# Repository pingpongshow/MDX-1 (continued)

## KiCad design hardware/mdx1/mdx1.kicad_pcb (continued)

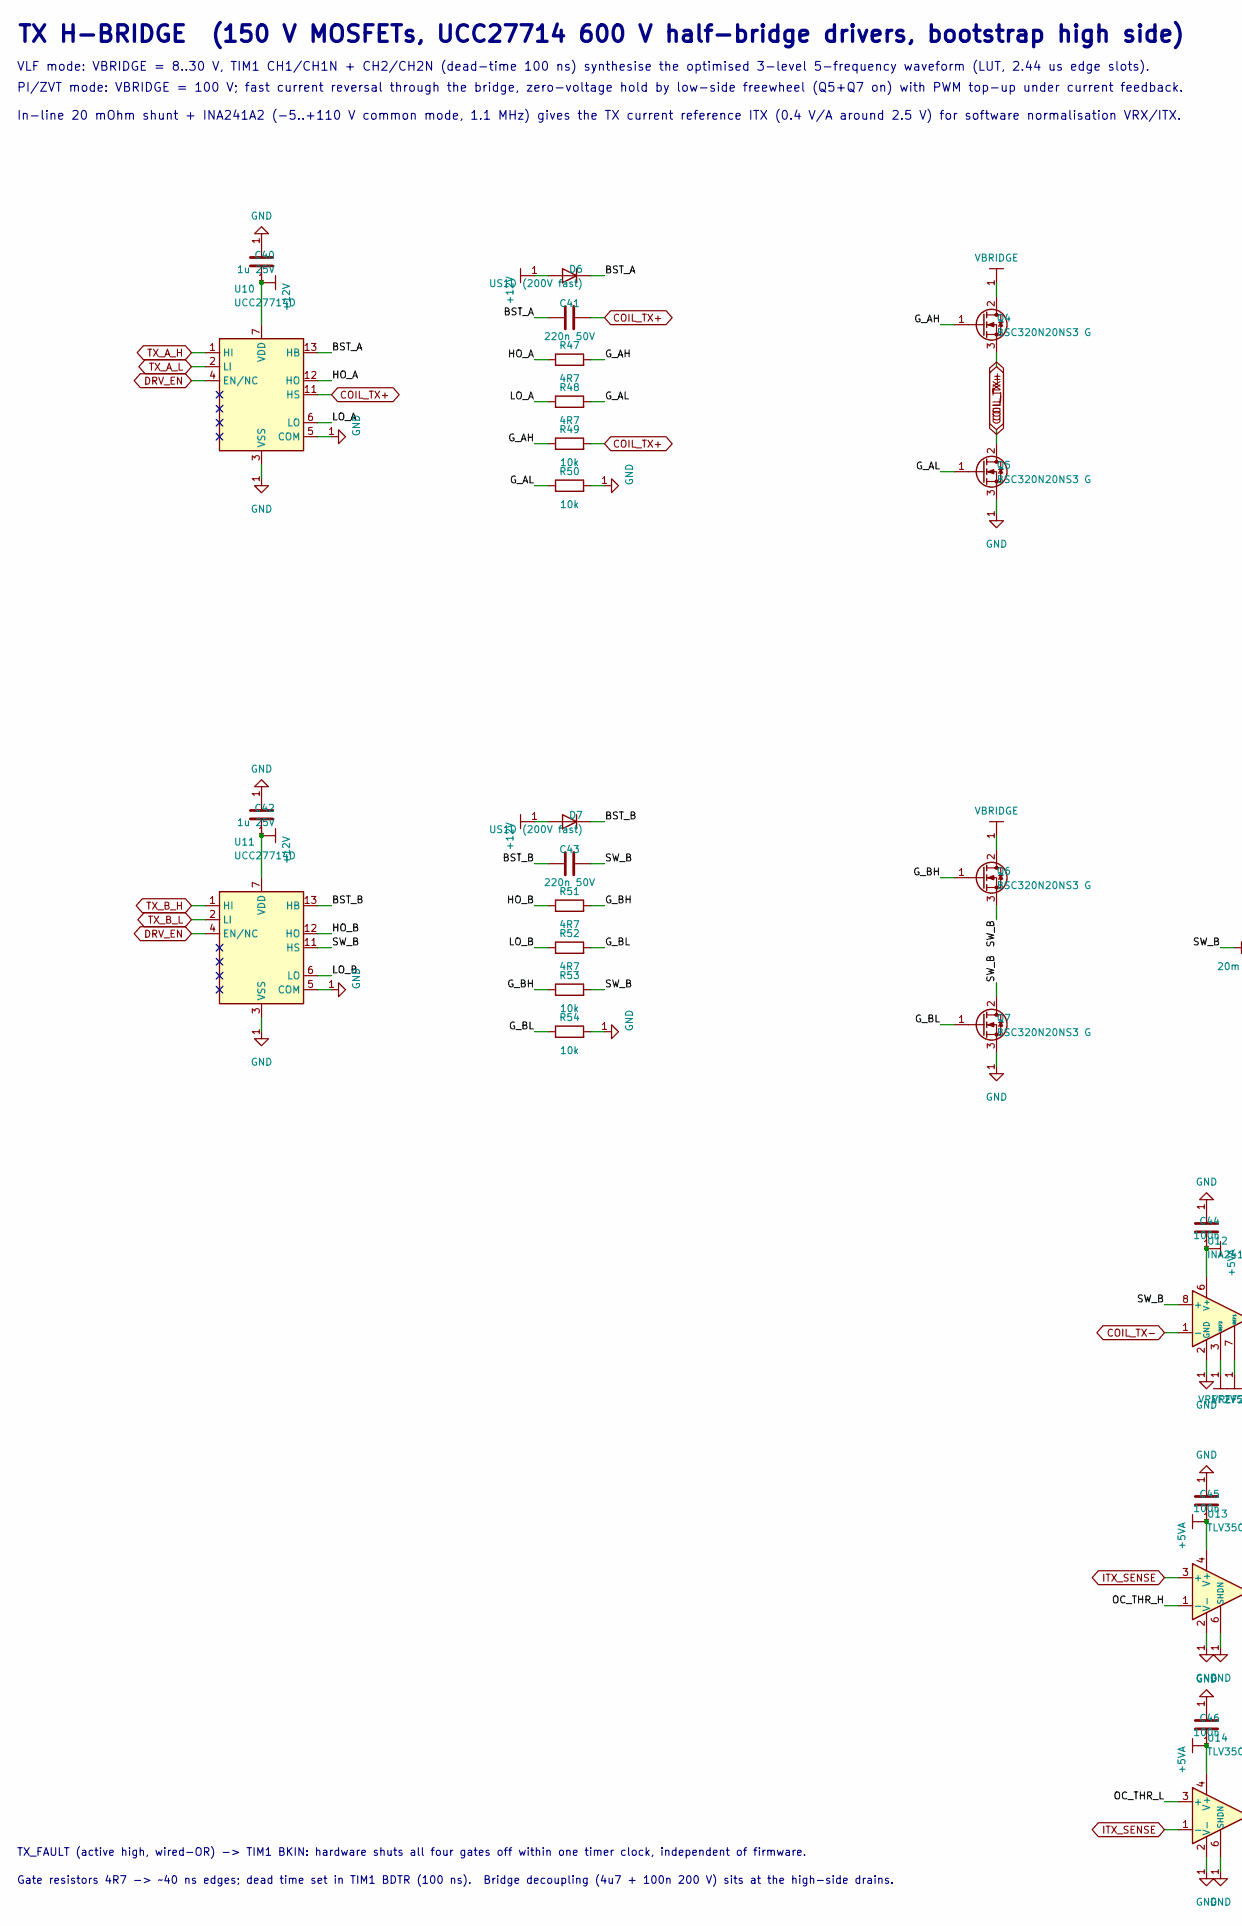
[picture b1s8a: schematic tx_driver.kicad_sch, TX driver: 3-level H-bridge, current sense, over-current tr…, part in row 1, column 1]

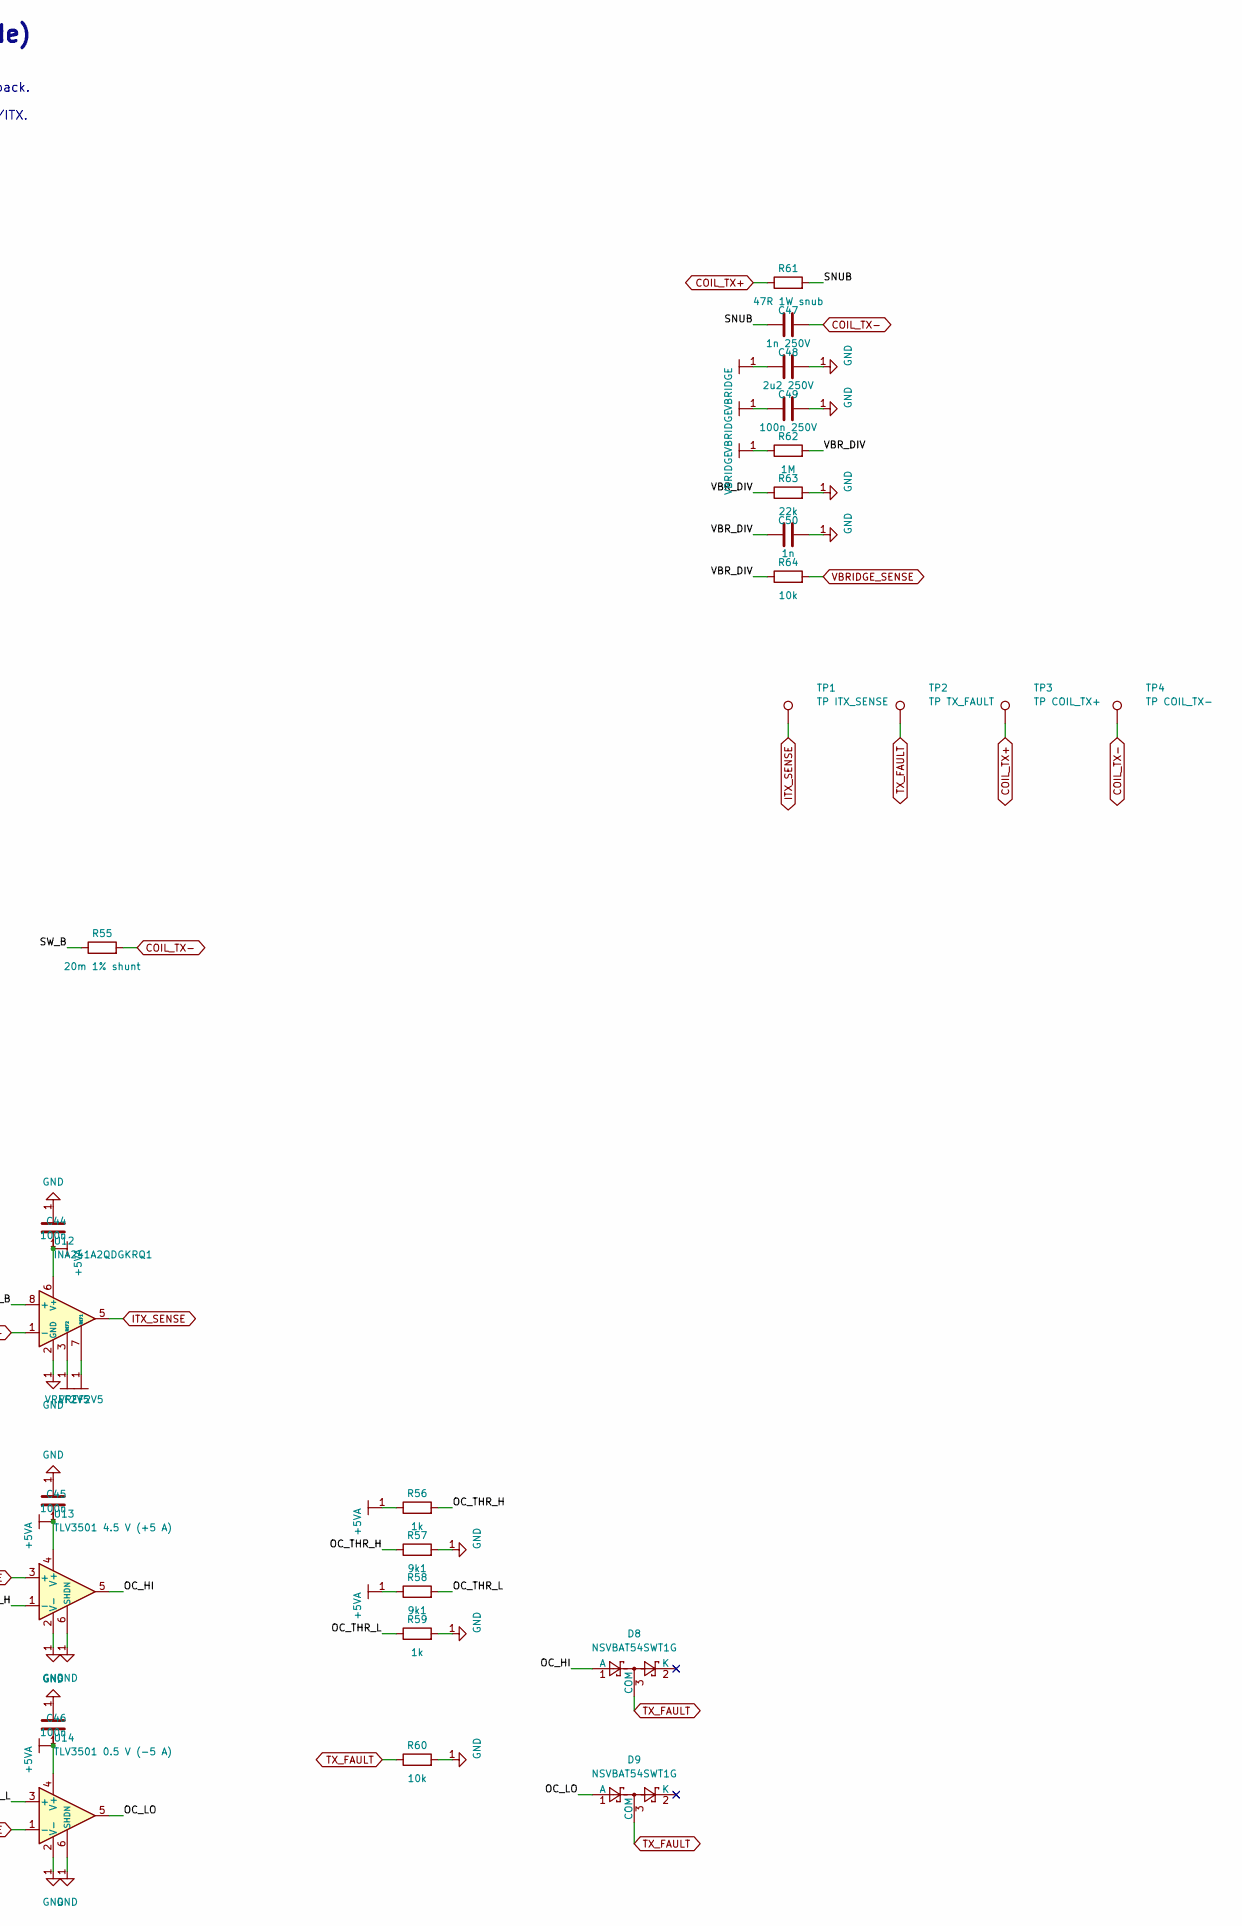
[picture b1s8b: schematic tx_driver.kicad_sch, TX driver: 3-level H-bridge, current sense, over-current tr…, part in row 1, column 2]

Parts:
C40, C42: 1u 25V; C_0603_1608Metric
C41, C43: 220n 50V; C_0603_1608Metric
C44, C45, C46: 100n; C_0402_1005Metric
C47: 1n 250V; C_1206_3216Metric
C48: 2u2 250V; C_2220_5750Metric
C49: 100n 250V; C_1206_3216Metric
C50: 1n; C_0402_1005Metric
D6, D7: US1D (200V fast); D_SMA
D8, D9: NSVBAT54SWT1G; SOT-323_SC-70
Q4, Q5, Q6, Q7: BSC320N20NS3 G; Infineon_PG-TDSON-8_6.15x5.15mm
R47, R48, R51, R52: 4R7; R_0402_1005Metric
R49, R50, R53, R54, R60, R64: 10k; R_0402_1005Metric
R55: 20m 1% shunt; R_2512_6332Metric
R56, R59: 1k; R_0402_1005Metric
R57, R58: 9k1; R_0402_1005Metric
R61: 47R 1W snub; R_2512_6332Metric
R62: 1M; R_0402_1005Metric
R63: 22k; R_0402_1005Metric
TP1: TP ITX_SENSE; TestPoint_Pad_D1.5mm
TP2: TP TX_FAULT; TestPoint_Pad_D1.5mm
TP3: TP COIL_TX+; TestPoint_Pad_D1.5mm
TP4: TP COIL_TX-; TestPoint_Pad_D1.5mm
U10, U11: UCC27714D; SOIC-14_3.9x8.7mm_P1.27mm
U12: INA241A2QDGKRQ1; VSSOP-8_3x3mm_P0.65mm
U13: TLV3501 4.5 V (+5 A); SOT-23-6
U14: TLV3501 0.5 V (-5 A); SOT-23-6

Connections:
+5VA: C44.1, C45.1, C46.1, R56.1, R58.1, U12.6 (V+), U13.4 (V+), U14.4 (V+); also elsewhere on the board
+12V: C40.1, C42.1, D6.2 (A), D7.2 (A), U10.7 (VDD), U11.7 (VDD); also elsewhere on the board
/TX driver: 3-level H-bridge, current sense, over-current trip/BST_A: C41.1, D6.1 (K), U10.13 (HB)
/TX driver: 3-level H-bridge, current sense, over-current trip/BST_B: C43.1, D7.1 (K), U11.13 (HB)
/TX driver: 3-level H-bridge, current sense, over-current trip/G_AH: Q4.1 (G), R47.2, R49.1
/TX driver: 3-level H-bridge, current sense, over-current trip/G_AL: Q5.1 (G), R48.2, R50.1
/TX driver: 3-level H-bridge, current sense, over-current trip/G_BH: Q6.1 (G), R51.2, R53.1
/TX driver: 3-level H-bridge, current sense, over-current trip/G_BL: Q7.1 (G), R52.2, R54.1
/TX driver: 3-level H-bridge, current sense, over-current trip/HO_A: R47.1, U10.12 (HO)
/TX driver: 3-level H-bridge, current sense, over-current trip/HO_B: R51.1, U11.12 (HO)
/TX driver: 3-level H-bridge, current sense, over-current trip/LO_A: R48.1, U10.6 (LO)
/TX driver: 3-level H-bridge, current sense, over-current trip/LO_B: R52.1, U11.6 (LO)
/TX driver: 3-level H-bridge, current sense, over-current trip/OC_HI: D8.1 (A), U13.5
/TX driver: 3-level H-bridge, current sense, over-current trip/OC_LO: D9.1 (A), U14.5
/TX driver: 3-level H-bridge, current sense, over-current trip/OC_THR_H: R56.2, R57.1, U13.1 (-)
/TX driver: 3-level H-bridge, current sense, over-current trip/OC_THR_L: R58.2, R59.1, U14.3 (+)
/TX driver: 3-level H-bridge, current sense, over-current trip/SNUB: C47.1, R61.2
/TX driver: 3-level H-bridge, current sense, over-current trip/SW_B: C43.2, Q6.3 (S), Q7.2 (D), R53.2, R55.1, U11.11 (HS), U12.8 (+)
/TX driver: 3-level H-bridge, current sense, over-current trip/VBR_DIV: C50.1, R62.2, R63.1, R64.1
COIL_TX+: C41.2, Q4.3 (S), Q5.2 (D), R49.2, R61.1, TP3.1 (1_1), U10.11 (HS); also elsewhere on the board
COIL_TX-: C47.2, R55.2, TP4.1 (1_1), U12.1 (-); also elsewhere on the board
DRV_EN: U10.4 (EN/NC), U11.4 (EN/NC); also elsewhere on the board
ITX_SENSE: TP1.1 (1_1), U12.5, U13.3 (+), U14.1 (-); also elsewhere on the board
TX_A_H: U10.1 (HI); also elsewhere on the board
TX_A_L: U10.2 (LI); also elsewhere on the board
TX_B_H: U11.1 (HI); also elsewhere on the board
TX_B_L: U11.2 (LI); also elsewhere on the board
TX_FAULT: D8.3 (COM), D9.3 (COM), R60.1, TP2.1 (1_1); also elsewhere on the board
VBRIDGE: C48.1, C49.1, Q4.2 (D), Q6.2 (D), R62.1; also elsewhere on the board
VBRIDGE_SENSE: R64.2; also elsewhere on the board
VREF2V5: U12.3 (REF2), U12.7 (REF1); also elsewhere on the board

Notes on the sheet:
TX_FAULT (active high, wired-OR) -> TIM1 BKIN: hardware shuts all four gates off within one timer clock, independent of firmware.
In-line 20 mOhm shunt + INA241A2 (-5..+110 V common mode, 1.1 MHz) gives the TX current reference ITX (0.4 V/A around 2.5 V) for software normalisation VRX/ITX.
Gate resistors 4R7 -> ~40 ns edges; dead time set in TIM1 BDTR (100 ns). Bridge decoupling (4u7 + 100n 200 V) sits at the high-side drains.
VLF mode: VBRIDGE = 8..30 V, TIM1 CH1/CH1N + CH2/CH2N (dead-time 100 ns) synthesise the optimised 3-level 5-frequency waveform (LUT, 2.44 us edge slots).
TX H-BRIDGE (150 V MOSFETs, UCC27714 600 V half-bridge drivers, bootstrap high side)
PI/ZVT mode: VBRIDGE = 100 V; fast current reversal through the bridge, zero-voltage hold by low-side freewheel (Q5+Q7 on) with PWM top-up under current feedback.

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
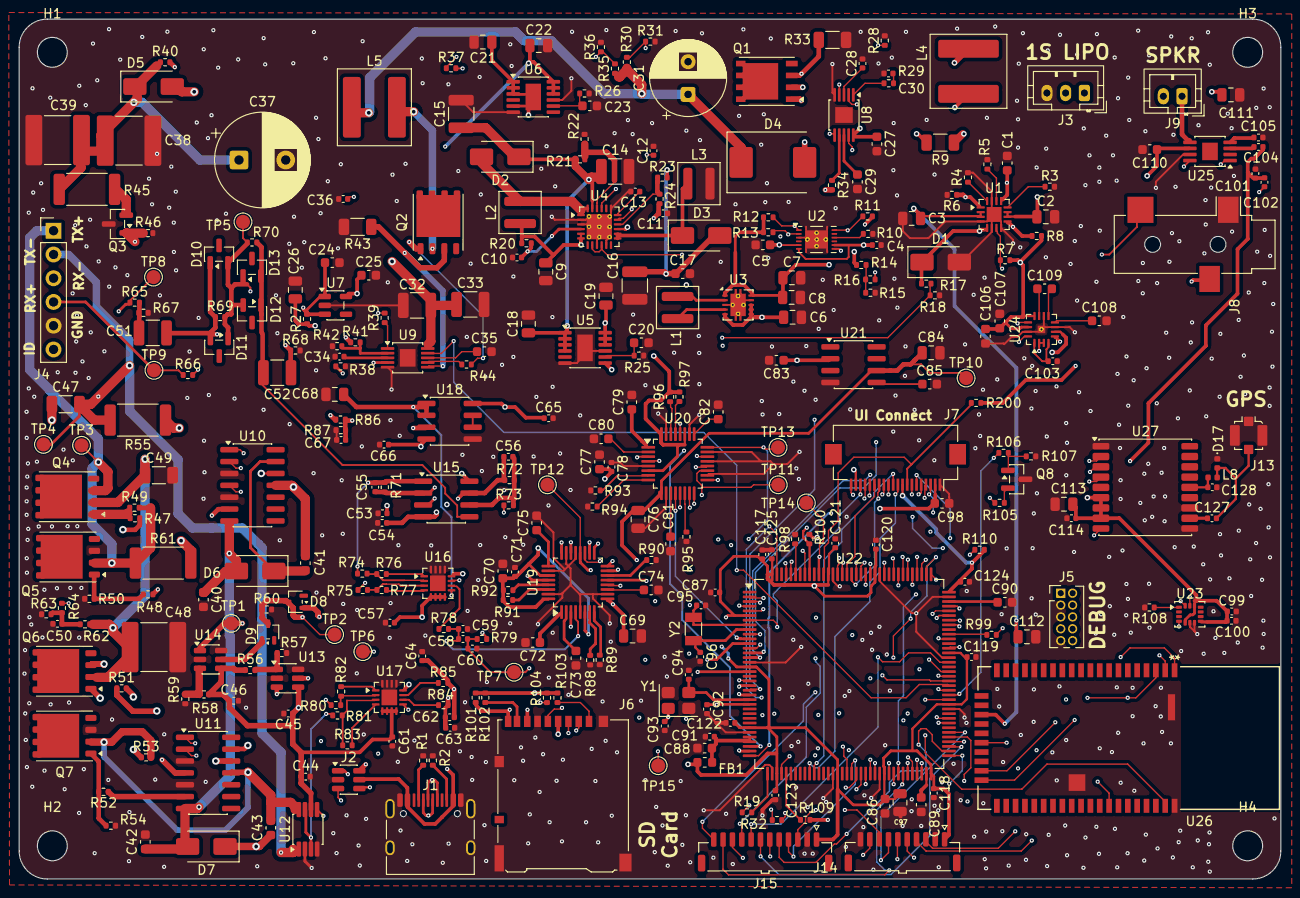
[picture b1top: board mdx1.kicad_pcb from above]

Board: 4 copper layers, 135.0 x 92.0 mm, 325 parts (0 on the bottom side), 250 nets.

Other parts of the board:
H1, H2, H3, H4: MountingHole_3.2mm_M3

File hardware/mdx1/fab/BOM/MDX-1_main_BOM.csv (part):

Comment,Designator,Footprint,Quantity,Manufacturer,MPN,LCSC Part #
"4.7 µF MLCC, 10 V X5R, 10 %","C1,C20,C23,C27,C29,C35,C86",C_0603_1608Metric,7,Taiyo Yuden,LMK107BJ475KA-T,
10 µF 10 V X5R MLCC,"C2,C3,C6,C9,C26,C68,C69,C76,C84,C97,C111,C112,C113",C_0805_2012Metric,13,Samsung Electro-Mechanics,CL21A106KPFNNNG,
100n,"C4,C10,C28,C44,C45,C46,C53,C54,C57,C61,C65,C66,C71,C78,C87,C91,C92,C99,C100,C114,C117,C118,C119,C120,C121,C122,C123,C124,C125",C_0402_1005Metric,29,Murata,GRM155R71H104KE14D,
"1 µF MLCC, 25 V X5R, 10 %","C5,C17,C24,C25,C40,C42,C70,C72,C73,C74,C75,C77,C79,C80,C81,C82,C83,C85,C88,C98,C108,C109,C110",C_0603_1608Metric,23,KYOCERA AVX,06033D105KAT2A,
22u 6.3V,"C7,C8",C_0805_2012Metric,2,TDK,C2012X5R0J226M085AB,
220n,"C11,C34,C104,C105",C_0402_1005Metric,4,Samsung Electro-Mechanics,CL05A224KP5NNNC,
"10 nF MLCC, 50 V X7R, 10 %","C12,C36,C128",C_0402_1005Metric,3,Murata,GRM155R71H103KA88D,
4n7,"C13,C30,C101",C_0402_1005Metric,3,Murata,GRM155R71H472KA01D,
22u 25V,"C14,C15,C16",C_1210_3225Metric,3,Samsung Electro-Mechanics,CL32A226KAJNNWE,
4u7 25V,"C18,C21",C_0805_2012Metric,2,TDK,C2012X5R1E475K125AB,
10u 25V,"C19,C22",C_0805_2012Metric,2,TDK,C2012X5R1V106K085AC,
100u 50V,C31,CP_Radial_D8.0mm_P3.50mm,1,Panasonic,EEU-FC1H101,
10u 50V,C32,C_1210_3225Metric,1,KEMET,C1210C106K5RACTU,
4u7 50V,C33,C_1210_3225Metric,1,Murata,GRM32ER71H475KA88L,
47u 160V,C37,CP_Radial_D10.0mm_P5.00mm,1,Rubycon,160PK47MEFC10X20,
2u2 250V,"C38,C39,C48",C_2220_5750Metric,3,TDK,C5750X7T2E225K250KE,
220n 50V,"C41,C43",C_0603_1608Metric,2,Murata,GRM188R71H224KAC4D,
1n 250V,C47,C_1206_3216Metric,1,Vishay,VPDD202W102K1GV001E,
100n 250V,C49,C_1206_3216Metric,1,Murata,GRM31CR72E104KW03L,
1n,C50,C_0402_1005Metric,1,TDK,C1005C0G1H102J050BA,
1u C0G/film,"C51,C52",C_1210_3225Metric,2,KYOCERA AVX,12103C105KAT2A,
680p C0G,"C55,C56",C_0402_1005Metric,2,Murata,GRM1555C1H681JA01D,
3n3 C0G,"C58,C62",C_0402_1005Metric,2,Murata,GRM1555C1H332JE01D,
330p C0G,"C59,C60,C63,C64",C_0402_1005Metric,4,Murata,GRM1555C1H331JA01D,
1u,"C67,C102,C103",C_0402_1005Metric,3,Samsung Electro-Mechanics,CL05A105KP5NNNC,
2u2,"C89,C90,C106,C107",C_0603_1608Metric,4,Murata,GRM188R61E225KA12D,
10p C0G,"C93,C94",C_0402_1005Metric,2,Murata,GRM1555C1H100JA01D,
6.8p C0G,"C95,C96",C_0402_1005Metric,2,Murata,GRM1555C1H6R8DA01D,
33 pF,C127,C_0402_1005Metric,1,Murata,GRM1555C1H330JA01D,
SMAJ5.0A TVS,D1,D_SMA,1,Littelfuse,SMAJ5.0A-E3/61,
SS34,"D2,D3",D_SMA,2,Vishay,SS34-E3/57T,
B560C 60V 5A,D4,D_SMC,1,Diodes Inc.,B560C-13-F,
STPS2150 150V,D5,D_SMA,1,STMicroelectronics,STPS2150A,
US1D,"D6,D7",D_SMA,2,Vishay,US1D-E3/61T,
NSVBAT54SWT1G,"D8,D9",SOT-323_SC-70,2,onsemi,NSVBAT54SWT1G,
BAS416,"D10,D11,D12,D13",SOT-23,4,Diodes Incorporated,BAS116-7-F,
PESD0402-140,D17,D_0402_1005Metric,1,Nexperia,PESD0402-140,
600R@100MHz,FB1,L_0603_1608Metric,1,Murata,BLM18KG601SN1D,
USB-C 16P,J1,USB_C_Receptacle_HRO_TYPE-C-31-M-12,1,GCT,USB4085-GF-A,
USBLC6-2SC6,J2,SOT-23-6,1,STMicroelectronics,USBLC6-2SC6,
Battery JST-PH 3p,J3,JST_PH_B3B-PH-K_1x03_P2.00mm_Vertical,1,JST,B3B-PH-K-S,
Coil header 1x06 2.54mm,J4,PinHeader_1x06_P2.54mm_Vertical,1,Wurth Elektronik,61300611121,
SWD 10p 1.27mm,J5,PinHeader_2x05_P1.27mm_Vertical,1,Samtec,FTSH-105-01-L-DV-K,
microSD,J6,microSD_HC_Hirose_DM3AT-SF-PEJM5,1,Hirose,DM3AT-SF-PEJM5,
UI link FFC 20p 0.5mm,J7,Hirose_FH12-20S-0.5SH_1x20-1MP_P0.50mm_Horizontal,1,Hirose,FH12-20S-0.5SH(55),
3.5 mm jack,J8,Jack_3.5mm_CUI_SJ-3523-SMT_Horizontal,1,CUI Devices,SJ-3523-SMT-TR,
Speaker 8R,J9,JST_PH_B2B-PH-K_1x02_P2.00mm_Vertical,1,JST,B2B-PH-K-S,
Conn_Coaxial,J13,U.FL_Molex_MCRF_73412-0110_Vertical,1,Molex,73412-0110,
1u5 XAL4020,L1,L_Coilcraft_XAL4020-XXX,1,Coilcraft,XAL4020-152MEC,
4u7 XAL4020,"L2,L3",L_Coilcraft_XAL4020-XXX,2,Coilcraft,XAL4030-472MEC,
22u XAL7050,L4,L_Coilcraft_XAL7050-XXX,1,Coilcraft,XAL7050-223MEC,
47u XAL7050,L5,L_Coilcraft_XAL7050-XXX,1,Coilcraft,XAL7050-473MEC,
27nH,L8,L_0402_1005Metric,1,Murata,LQW15AN27NG00D,
SiR680ADP-T1-UE3,Q1,PowerPAK_SO-8_Single,1,Vishay Siliconix,SIR680ADP-T1-UE3,
BSC190N15NS3,Q2,Infineon_PG-TDSON-8_6.15x5.15mm,1,Infineon,BSC190N15NS3GATMA1,
BSS127S,Q3,SOT-23,1,Diodes Incorporated,BSS127S-7,
BSC320N20NS3 G,"Q4,Q5,Q6,Q7",Infineon_PG-TDSON-8_6.15x5.15mm,4,Infineon,BSC320N20NS3GATMA1,
2N7002,Q8,SOT-23,1,onsemi,2N7002ET1G,
5k1,"R1,R2",R_0402_1005Metric,2,Yageo,RC0402FR-075K1L,
1k1,R3,R_0402_1005Metric,1,Yageo,RC0402FR-071K1L,
887R,R4,R_0402_1005Metric,1,Yageo,RC0402FR-07887RL,
47k,"R5,R17,R36,R101,R102,R103,R104",R_0402_1005Metric,7,Yageo,RC0402FR-0747KL,
10k,"R6,R10,R11,R16,R19,R37,R49,R50,R53,R54,R60,R64,R89,R94,R98,R200",R_0402_1005Metric,16,Yageo,RC0402FR-0710KL,
100k,"R7,R8,R14,R15,R24,R46,R69,R70,R90,R91,R92,R95,R96,R97,R107,R110",R_0402_1005Metric,16,Yageo,RC0402FR-07100KL,
10m 1%,R9,R_1206_3216Metric,1,Vishay Dale,WSL1206R0100FEA,
4k7,"R12,R13,R100,R109",R_0402_1005Metric,4,Yageo,RC0402FR-074K7L,
22k,"R18,R29,R39,R63",R_0402_1005Metric,4,Yageo,RC0402FR-0722KL,
100R,"R20,R78,R79,R84,R85,R106",R_0402_1005Metric,6,Yageo,RC0402FR-07100RL,
1M,"R21,R62,R67,R68",R_0402_1005Metric,4,Yageo,RC0402FR-071ML,
113k,R22,R_0402_1005Metric,1,Yageo,RC0402FR-07113KL,
499k,R23,R_0402_1005Metric,1,Yageo,RC0402FR-07499KL,
49k9 0.1% SET,"R25,R26",R_0402_1005Metric,2,Panasonic,ERA-2AEB4992X,
10R,"R27,R34,R44",R_0402_1005Metric,3,Yageo,RC0402FR-0710RL,
41k2,R28,R_0402_1005Metric,1,Yageo,RC0402FR-0741K2L,
442k,"R30,R35",R_0402_1005Metric,2,Yageo,RC0402FR-07442KL,
40k2,R31,R_0402_1005Metric,1,Bourns,CR0402-FX-4022GLF,
66k5,R32,R_0402_1005Metric,1,Yageo,RC0402FR-0766K5L,
20m,R33,R_1206_3216Metric,1,Vishay Dale,WSL1206R0200FEA,
140k,R38,R_0402_1005Metric,1,Yageo,RC0402FR-07140KL,
619k,"R40,R41",R_0402_1005Metric,2,Yageo,RC0402FR-07619KL,
20k0,R42,R_0402_1005Metric,1,Yageo,RC0402FR-0720KL,
50m,R43,R_1206_3216Metric,1,Vishay Dale,WSL1206R0500FEA,
10k 1W,R45,R_2512_6332Metric,1,Bourns,CR2512-FX-1002ELF,
4R7,"R47,R48,R51,R52",R_0402_1005Metric,4,Yageo,RC0402FR-074R7L,
20m 1% shunt,R55,R_2512_6332Metric,1,Vishay Dale,WSL2512R0200FEA,
1k,"R56,R59",R_0402_1005Metric,2,Yageo,RC0402FR-071KL,
9k1,"R57,R58",R_0402_1005Metric,2,Yageo,RC0402FR-079K1L,
47R 1W snub,R61,R_2512_6332Metric,1,Vishay Dale,CRCW251247R0FKEG,
47R,"R65,R66",R_0402_1005Metric,2,Bourns,CR0402-FX-47R0GLF,
1k 0.1%,"R71,R72,R74,R75,R76,R77,R80,R81,R82,R83",R_0402_1005Metric,10,Panasonic,ERA-2VEB1001X,
105R 0.1%,R73,R_0402_1005Metric,1,Panasonic,ERA-2AEB1050X,
5k11 0.1%,R86,R_0402_1005Metric,1,Panasonic,ERA-2AEB5111X,
10k 0.1%,R87,R_0402_1005Metric,1,Panasonic,ERA-2VEB1002X,
60k4,"R88,R93",R_0402_1005Metric,2,Yageo,RC0402FR-0760K4L,
33R,R99,R_0402_1005Metric,1,Yageo,RC0402FR-0733RL,
22R,R105,R_0402_1005Metric,1,Yageo,RC0402FR-0722RL,
0R,R108,R_0402_1005Metric,1,Yageo,RC0402JR-070RL,
BQ24075RGT,U1,VQFN-16-1EP_3x3mm_P0.5mm_EP1.6x1.6mm,1,Texas Instruments,BQ24075RGTR,
BQ27441DRZT-G1A,U2,Texas_S-PDSO-N12,1,Texas Instruments,BQ27441DRZT-G1A,
TPS63001,U3,Texas_DRC0010J_ThermalVias,1,Texas Instruments,TPS63001DRCR,
TPS65131RGET,U4,Texas_RGE0024H_VQFN-24-1EP_4x4mm_P0.5mm_EP2.7x2.7mm_ThermalVias,1,Texas Instruments,TPS65131RGET,
LT3045,U5,MSOP-12-1EP_3x4.039mm_P0.65mm_EP1.651x2.845mm,1,Analog Devices,LT3045EMSE#PBF,
LT3094,U6,MSOP-12-1EP_3x4.039mm_P0.65mm_EP1.651x2.845mm,1,Analog Devices,LT3094EMSE#PBF,
TPS7A2033,U7,SOT-23-5,1,Texas Instruments,LP5907MFX-3.3/NOPB,
LT3757,"U8,U9",MSOP-10-1EP_3x3mm_P0.5mm_EP1.68x1.88mm,2,Analog Devices,LT3757EMSE#PBF,
UCC27714D,"U10,U11",SOIC-14_3.9x8.7mm_P1.27mm,2,Texas Instruments,UCC27714D,
INA241A2QDGKRQ1,U12,VSSOP-8_3x3mm_P0.65mm,1,Texas Instruments,INA241A2QDGKRQ1,
4.5 ns rail-to-rail comparator,"U13,U14",SOT-23-6,2,Texas Instruments,TLV3501AIDBVR,
OPA1612,U15,SOIC-8_3.9x4.9mm_P1.27mm,1,Texas Instruments,OPA1612AIDR,
THS4551,"U16,U17",VQFN-16-1EP_3x3mm_P0.5mm_EP1.68x1.68mm,2,Texas Instruments,THS4551IRGTR,
OPA1656,U18,SOIC-8_3.9x4.9mm_P1.27mm,1,Texas Instruments,OPA1656IDR,
ADS127L01,"U19,U20",TQFP-32_5x5mm_P0.5mm,2,Texas Instruments,ADS127L01IPBSR,
REF5025,U21,SOIC-8_3.9x4.9mm_P1.27mm,1,Texas Instruments,REF5025ID,
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
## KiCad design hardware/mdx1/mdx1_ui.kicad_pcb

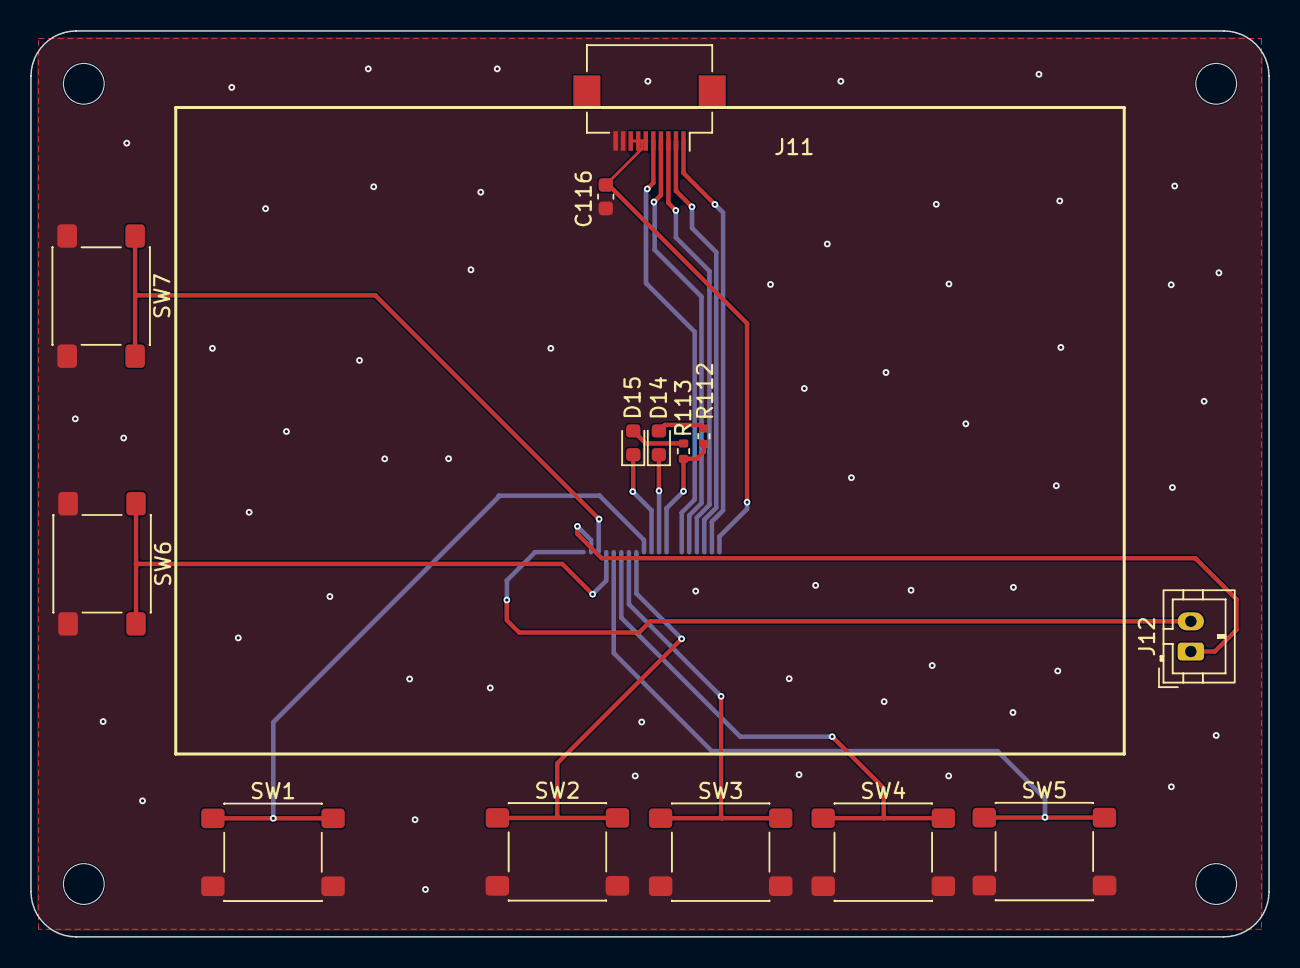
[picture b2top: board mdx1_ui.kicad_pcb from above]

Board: 2 copper layers, 82.0 x 60.0 mm, 19 parts (1 on the bottom side), 21 nets.

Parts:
C116: 1u; C_0603_1608Metric
D14: LED green; LED_0603_1608Metric
D15: LED amber; LED_0603_1608Metric
H1, H2, H3, H4: MountingHole_2.7mm_M2.5
J10: UI link FFC 20p 0.5mm; Hirose_FH12-20S-0.5SH_1x20-1MP_P0.50mm_Horizontal
J11: LCD FPC 10p 0.5mm; Hirose_FH12-10S-0.5SH_1x10-1MP_P0.50mm_Horizontal
J12: Front-light LED; JST_PH_B2B-PH-K_1x02_P2.00mm_Vertical
R112, R113: 1k; R_0402_1005Metric
SW1: MENU; SW_SPST_PTS645Sx43SMTR92
SW2: UP; SW_SPST_PTS645Sx43SMTR92
SW3: DOWN; SW_SPST_PTS645Sx43SMTR92
SW4: LEFT; SW_SPST_PTS645Sx43SMTR92
SW5: RIGHT; SW_SPST_PTS645Sx43SMTR92
SW6: PINPOINT; SW_SPST_PTS645Sx43SMTR92
SW7: POWER; SW_SPST_PTS645Sx43SMTR92

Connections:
+3V3: J10.9, R112.1, R113.1
+5V_LCD: C116.1, J10.2, J11.6, J11.7, J11.8
/UI board (separate PCB): memory LCD, 6-key pad + pinpoint + power, LEDs, front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: D14.2, R112.2
/UI board (separate PCB): memory LCD, 6-key pad + pinpoint + power, LEDs, front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: D15.2, R113.2
DISP_CS: J10.5, J11.3
DISP_EN: J10.7, J11.5
DISP_EXTCOM: J10.6, J11.4
DISP_MOSI: J10.4, J11.2
DISP_SCK: J10.3, J11.1
FL_K: J10.20, J12.2
GND: C116.2, J10.1, J10.8, J11.9, J11.10, SW1.2, SW2.2, SW3.2, SW4.2, SW5.2, SW6.2, SW7.2
KEY_DOWN: J10.14, SW3.1
KEY_LEFT: J10.15, SW4.1
KEY_MENU: J10.12, SW1.1
KEY_PP: J10.17, SW6.1
KEY_PWR: J10.18, SW7.1
KEY_RIGHT: J10.16, SW5.1
KEY_UP: J10.13, SW2.1
LED_CHG: D15.1, J10.11
LED_STAT: D14.1, J10.10
VSYS: J10.19, J12.1

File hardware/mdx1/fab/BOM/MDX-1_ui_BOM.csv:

Comment,Designator,Footprint,Quantity,Manufacturer,MPN,LCSC Part #
1u,C116,C_0603_1608Metric,1,KYOCERA AVX,06033D105KAT2A,
LED green,D14,LED_0603_1608Metric,1,Kingbright,APT1608SGC,
LED amber,D15,LED_0603_1608Metric,1,Kingbright,APT1608SYCK,
UI link FFC 20p 0.5mm,J10,Hirose_FH12-20S-0.5SH_1x20-1MP_P0.50mm_Horizontal,1,Hirose,FH12-20S-0.5SH(55),
LCD FPC 10p 0.5mm,J11,Hirose_FH12-10S-0.5SH_1x10-1MP_P0.50mm_Horizontal,1,Hirose,FH12-10S-0.5SH(55),
Front-light LED,J12,JST_PH_B2B-PH-K_1x02_P2.00mm_Vertical,1,JST,B2B-PH-K-S,
1k,"R112,R113",R_0402_1005Metric,2,Yageo,RC0402FR-071KL,
"6x6 mm tactile switch, 4.3 mm","SW1,SW2,SW3,SW4,SW5,SW6,SW7",SW_SPST_PTS645Sx43SMTR92,7,C&K,PTS645SK43SMTR92 LFS,
